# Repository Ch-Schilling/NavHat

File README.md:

# NavHat
NavHat or Navigaion Hat is a Raspberry Pi HAT made for saling boats. The HAT implements a number of features to make the Raspberry Pi suitable for a sailing boat environment. It provides power to the Raspberry Pi from board supply, collects data from NMEA bus and attached sensors. It provides the hardware base for an Open Source Navigation platform.

**Features:**
* Powered by board supply of 12-28V DC
* Onboard fuses for Raspberry and power outputs
* Four Power Outputs of up to 6A with current and temperature monitoring
* Very low sleep current
* Wake-up by key or RTC
* barometric sensor
* CAN interface for NMEA2000 network
* RS232 and RS422 interfaces for NMEA0183 devices
* Sensor interfaces with STEMMA and Qwiic compatibility
* Designed for compatibility to Raspberry Pi HAT specification

The board is designed using KiCad. 
For more details, see the corresponding [documentation](./documentation/NavHAT.md).

I hope you like the project as much as I do. In case of interest of the board itself, please contact me.

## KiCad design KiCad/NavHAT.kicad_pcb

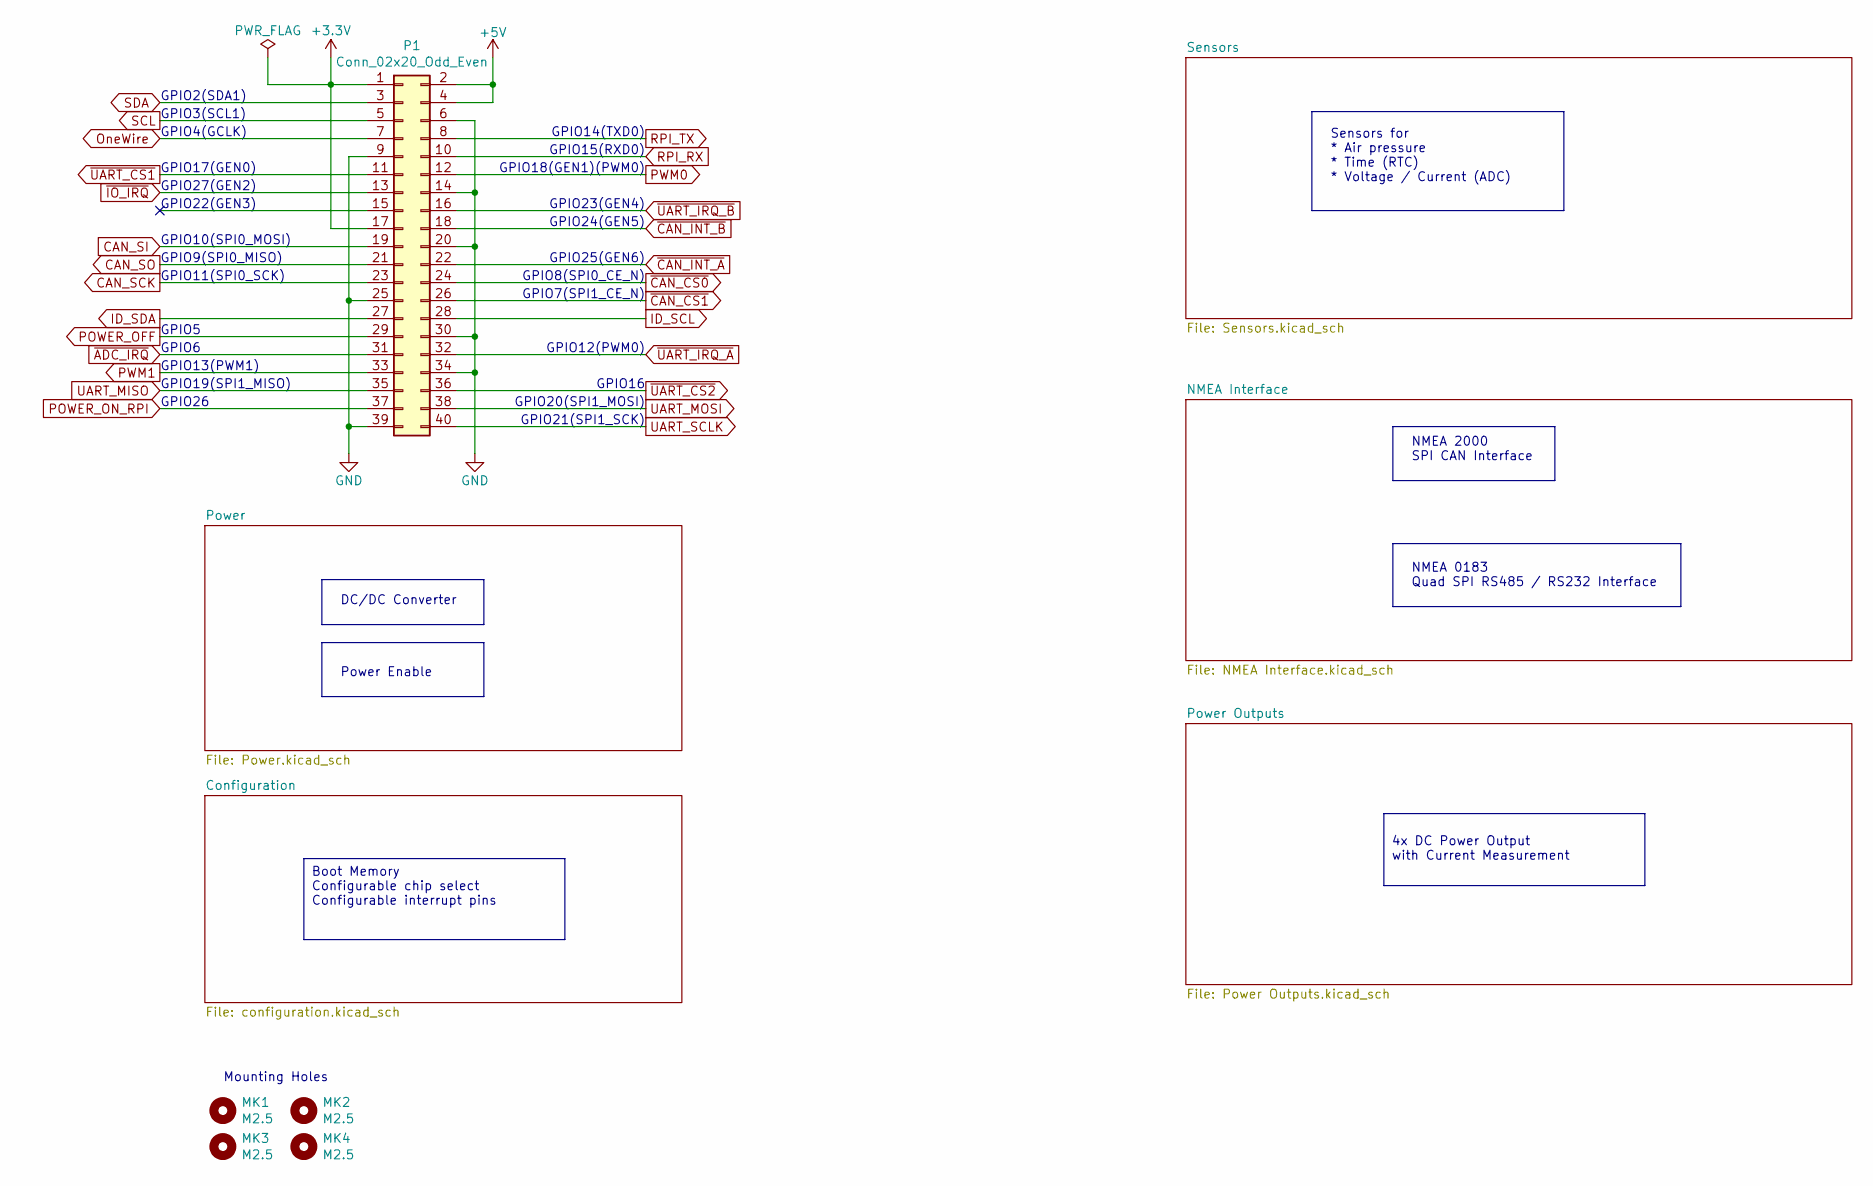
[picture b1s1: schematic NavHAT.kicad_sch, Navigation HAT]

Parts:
MK1, MK2, MK3, MK4: M2.5; MountingHole_2.7mm_M2.5
P1: Conn_02x20_Odd_Even; PinSocket_2x20_P2.54mm_Vertical

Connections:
+3.3V: P1.1, P1.17; also elsewhere on the board
+5V: P1.2, P1.4; also elsewhere on the board
CAN_SCK: P1.23; also elsewhere on the board
CAN_SI: P1.19; also elsewhere on the board
CAN_SO: P1.21; also elsewhere on the board
GND: P1.6, P1.9, P1.14, P1.20, P1.25, P1.30, P1.34, P1.39; also elsewhere on the board
ID_SCL: P1.28; also elsewhere on the board
ID_SDA: P1.27; also elsewhere on the board
OneWire: P1.7; also elsewhere on the board
POWER_OFF: P1.29; also elsewhere on the board
POWER_ON_RPI: P1.37; also elsewhere on the board
PWM0: P1.12; also elsewhere on the board
PWM1: P1.33; also elsewhere on the board
RPI_RX: P1.10; also elsewhere on the board
RPI_TX: P1.8; also elsewhere on the board
SCL: P1.5; also elsewhere on the board
SDA: P1.3; also elsewhere on the board
UART_MISO: P1.35; also elsewhere on the board
UART_MOSI: P1.38; also elsewhere on the board
UART_SCLK: P1.40; also elsewhere on the board
~ADC_IRQ: P1.31; also elsewhere on the board
~CAN_CS0: P1.24; also elsewhere on the board
~CAN_CS1: P1.26; also elsewhere on the board
~CAN_INT_A: P1.22; also elsewhere on the board
~CAN_INT_B: P1.18; also elsewhere on the board
~IO_IRQ: P1.13; also elsewhere on the board
~UART_CS1: P1.11; also elsewhere on the board
~UART_CS2: P1.36; also elsewhere on the board
~UART_IRQ_A: P1.32; also elsewhere on the board
~UART_IRQ_B: P1.16; also elsewhere on the board

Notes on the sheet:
Boot Memory Configurable chip select Configurable interrupt pins
4x DC Power Output with Current Measurement
NMEA 2000 SPI CAN Interface
GPIO26
GPIO8(SPI0_CE_N)
GPIO18(GEN1)(PWM0)
GPIO14(TXD0)
GPIO2(SDA1)
GPIO22(GEN3)
GPIO10(SPI0_MOSI)
GPIO16
GPIO6
Power Enable
GPIO5
GPIO23(GEN4)
GPIO3(SCL1)
GPIO9(SPI0_MISO)
Mounting Holes
GPIO24(GEN5)
GPIO11(SPI0_SCK)
GPIO13(PWM1)
GPIO21(SPI1_SCK)
GPIO20(SPI1_MOSI)
NMEA 0183 Quad SPI RS485 / RS232 Interface
GPIO17(GEN0)
GPIO7(SPI1_CE_N)
GPIO4(GCLK)
GPIO19(SPI1_MISO)
GPIO12(PWM0)
Sensors for * Air pressure * Time (RTC) * Voltage / Current (ADC)
GPIO25(GEN6)
GPIO27(GEN2)
GPIO15(RXD0)
DC/DC Converter

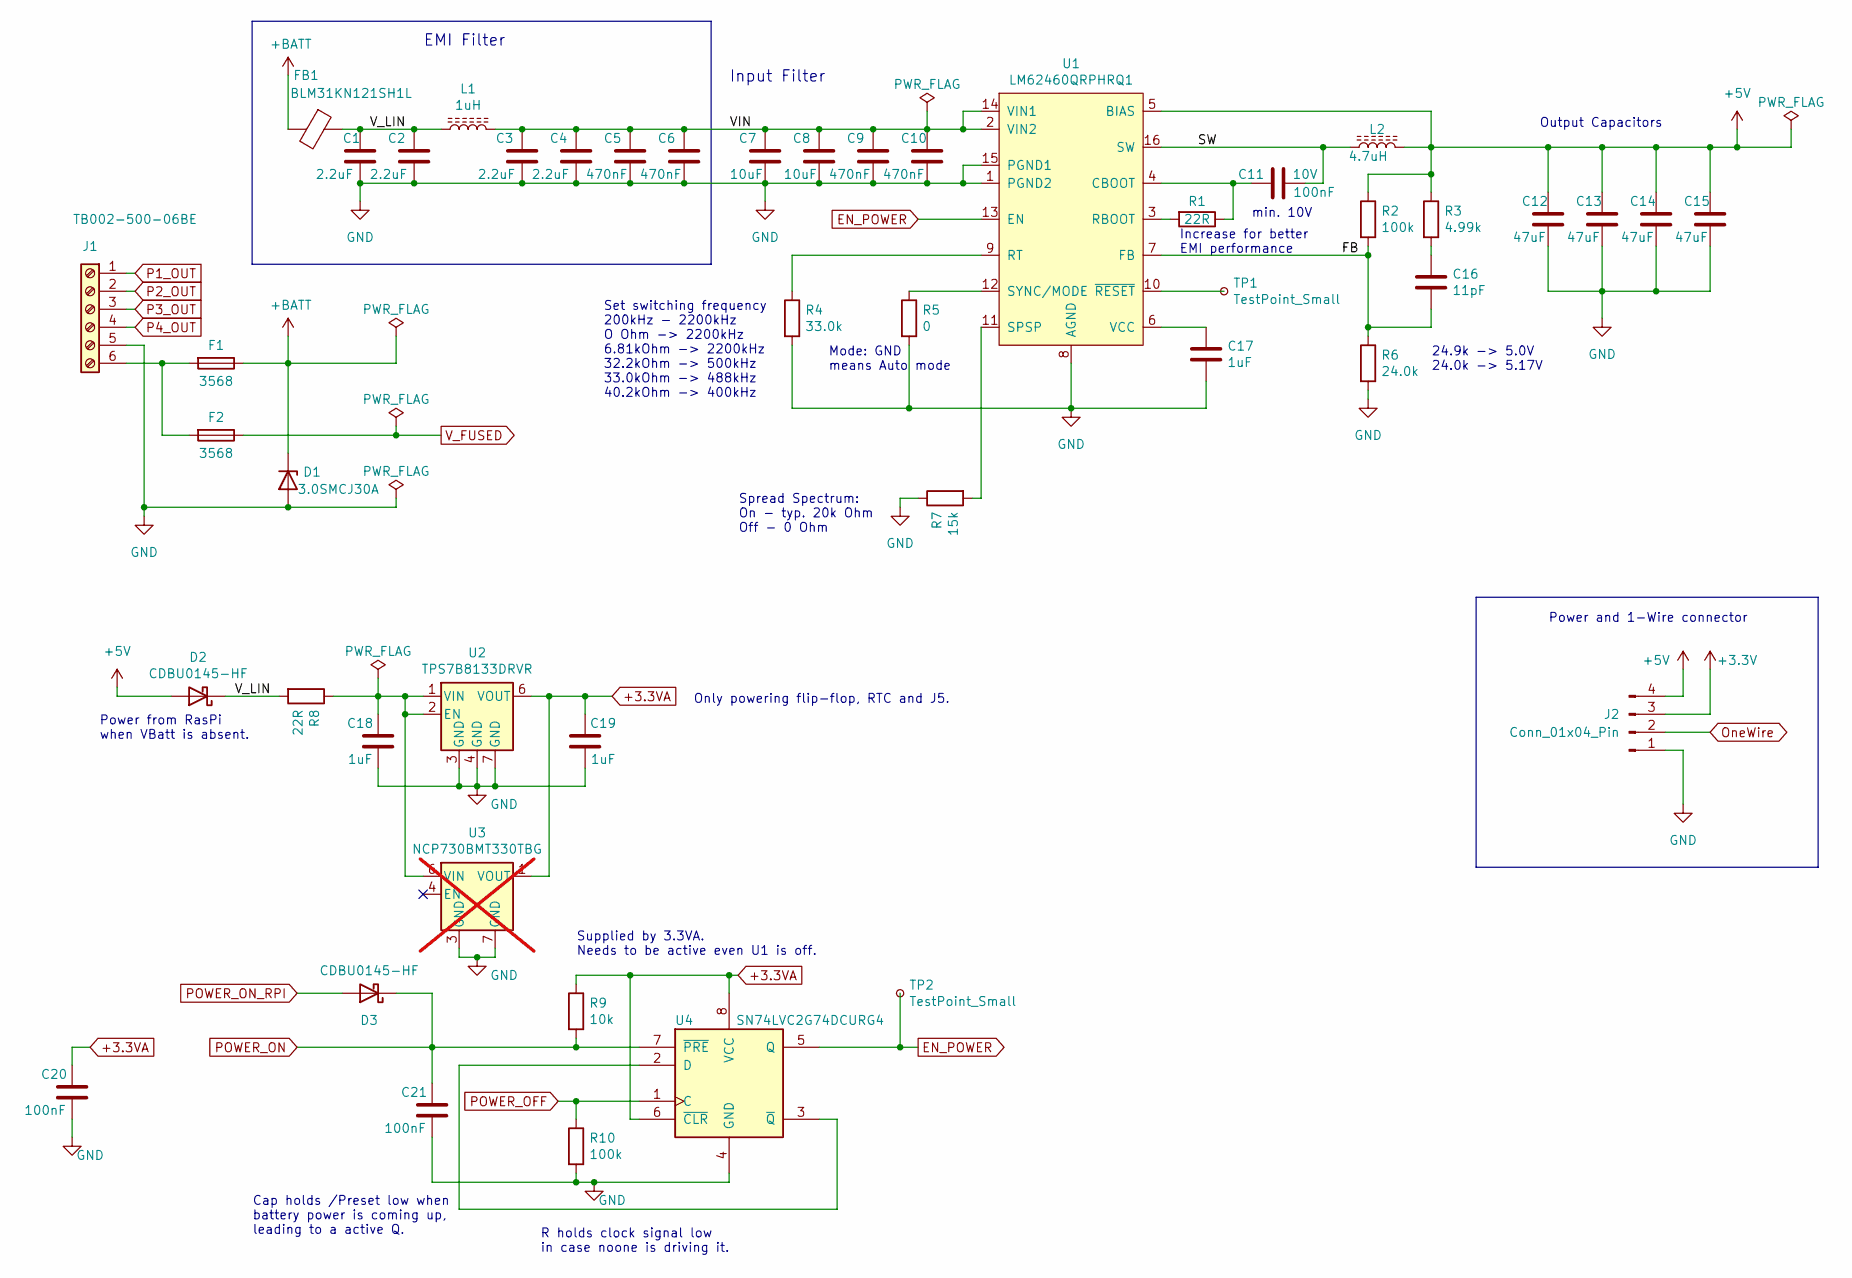
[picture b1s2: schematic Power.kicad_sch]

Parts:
C1, C2, C3, C4: 2.2uF; C_1210_3225Metric; Voltage Rating 50V
C5, C6, C9, C10: 470nF; C_0603_1608Metric; Voltage Rating 50V
C7, C8: 10uF; C_1210_3225Metric; Voltage Rating 50V
C11: 100nF; C_0402_1005Metric; Voltage Rating 10V
C12, C13, C14, C15: 47uF; C_1210_3225Metric; Voltage Rating 10V
C16: 11pF; C_0402_1005Metric
C17: 1uF; C_0603_1608Metric
C18: 1uF; C_0402_1005Metric; Voltage Rating 50V
C19: 1uF; C_0402_1005Metric
C20, C21: 100nF; C_0402_1005Metric
D1: 3.0SMCJ30A; D_SMC; Voltage Rating 30V
D2, D3: CDBU0145-HF; D_0603_1608Metric
F1, F2: 3568; Fuseholder_Blade_Mini_Keystone_3568
FB1: BLM31KN121SH1L; C_1206_3216Metric
J1: TB002-500-06BE; TerminalBlock_Phoenix_MKDS-1,5-6_1x06_P5.00mm_Horizontal
J2: Conn_01x04_Pin; PinHeader_1x04_P2.54mm_Vertical
L1: 1uH; WE-LHMI-5030; MPN 74437336010
L2: 4.7uH; WE-XHMI-6060; MPN 74439346047
R1, R8: 22R; R_0402_1005Metric
R2, R10: 100k; R_0402_1005Metric
R3: 4.99k; R_0402_1005Metric
R4: 33.0k; R_0402_1005Metric
R5: 0; R_0402_1005Metric
R6: 24.0k; R_0402_1005Metric
R7: 15k; R_0402_1005Metric
R9: 10k; R_0402_1005Metric
TP1, TP2: TestPoint_Small; TestPoint_THTPad_D1.0mm_Drill0.5mm
U1: LM62460QRPHRQ1; VQFN-HR-16
U2: TPS7B8133DRVR; DFN-6-1EP_2x2mm_P0.65mm_EP1x1.6mm
U3: NCP730BMT330TBG; DFN-6-1EP_2x2mm_P0.65mm_EP1x1.6mm; not fitted
U4: SN74LVC2G74DCURG4; VSSOP-8_2.4x2.1mm_P0.5mm

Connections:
+3.3V: J2.3; also elsewhere on the board
+3.3VA: C19.2, C20.2, R9.1, U2.6 (VOUT), U3.1 (VOUT), U4.6 (~CLR), U4.8 (VCC); also elsewhere on the board
+5V: C12.1, C13.1, C14.1, C15.1, D2.2 (A), J2.4, L2.2, R2.1, R3.1, U1.5 (BIAS); also elsewhere on the board
+BATT: D1.1 (K), F1.1, FB1.2
/Power/FB: C16.2, R2.2, R6.1, U1.7 (FB)
/Power/SW: C11.1, L2.1, U1.16 (SW)
/Power/VIN: C3.1, C4.1, C5.1, C6.1, C7.1, C8.1, C9.1, C10.1, L1.2, U1.2 (VIN2), U1.14 (VIN1)
/Power/V_LIN: C1.1, C2.1, D2.1 (K), FB1.1, L1.1, R8.2
EN_POWER: TP2.1, U1.13 (EN), U4.5 (Q)
GND: C1.2, C2.2, C3.2, C4.2, C5.2, C6.2, C7.2, C8.2, C9.2, C10.2, C12.2, C13.2, C14.2, C15.2, C17.2, C18.1, C19.1, C20.1, C21.1, D1.2 (A), J1.5, J2.1, R4.2, R5.2, R6.2, R7.1, R10.2, U1.1 (PGND2), U1.8 (AGND), U1.15 (PGND1), U2.3 (GND), U2.4 (GND), U2.7 (GND), U3.3 (GND), U3.7 (GND), U4.4 (GND); also elsewhere on the board
unnamed: C16.1, R3.2
unnamed: F1.2, F2.2, J1.6
unnamed: C11.2, R1.1, U1.4 (CBOOT)
unnamed: R1.2, U1.3 (RBOOT)
unnamed: R4.1, U1.9 (RT)
unnamed: R7.2, U1.11 (SPSP)
unnamed: R5.1, U1.12 (SYNC/MODE)
unnamed: C17.1, U1.6 (VCC)
unnamed: TP1.1, U1.10 (~RESET)
unnamed: C18.2, R8.1, U2.1 (VIN), U2.2 (EN), U3.6 (VIN)
unnamed: U4.2 (D), U4.3 (~Q)
OneWire: J2.2; also elsewhere on the board
P1_OUT: J1.1; also elsewhere on the board
P2_OUT: J1.2; also elsewhere on the board
P3_OUT: J1.3; also elsewhere on the board
P4_OUT: J1.4; also elsewhere on the board
POWER_OFF: R10.1, U4.1 (C); also elsewhere on the board
POWER_ON: C21.2, D3.1 (K), R9.2, U4.7 (~PRE); also elsewhere on the board
POWER_ON_RPI: D3.2 (A); also elsewhere on the board
V_FUSED: F2.1; also elsewhere on the board

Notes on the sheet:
Increase for better EMI performance
Only powering flip-flop, RTC and J5.
Spread Spectrum: On - typ. 20k Ohm Off - 0 Ohm
Supplied by 3.3VA. Needs to be active even U1 is off.
Output Capacitors
Power and 1-Wire connector
Input Filter
min. 10V
EMI Filter
Power from RasPi when VBatt is absent.
Mode: GND means Auto mode
Set switching frequency 200kHz - 2200kHz O Ohm -> 2200kHz 6.81kOhm -> 2200kHz 32.2kOhm -> 500kHz 33.0kOhm -> 488kHz 40.2kOhm -> 400kHz
Cap holds /Preset low when battery power is coming up, leading to a active Q.
R holds clock signal low in case noone is driving it.
24.9k -> 5.0V 24.0k -> 5.17V

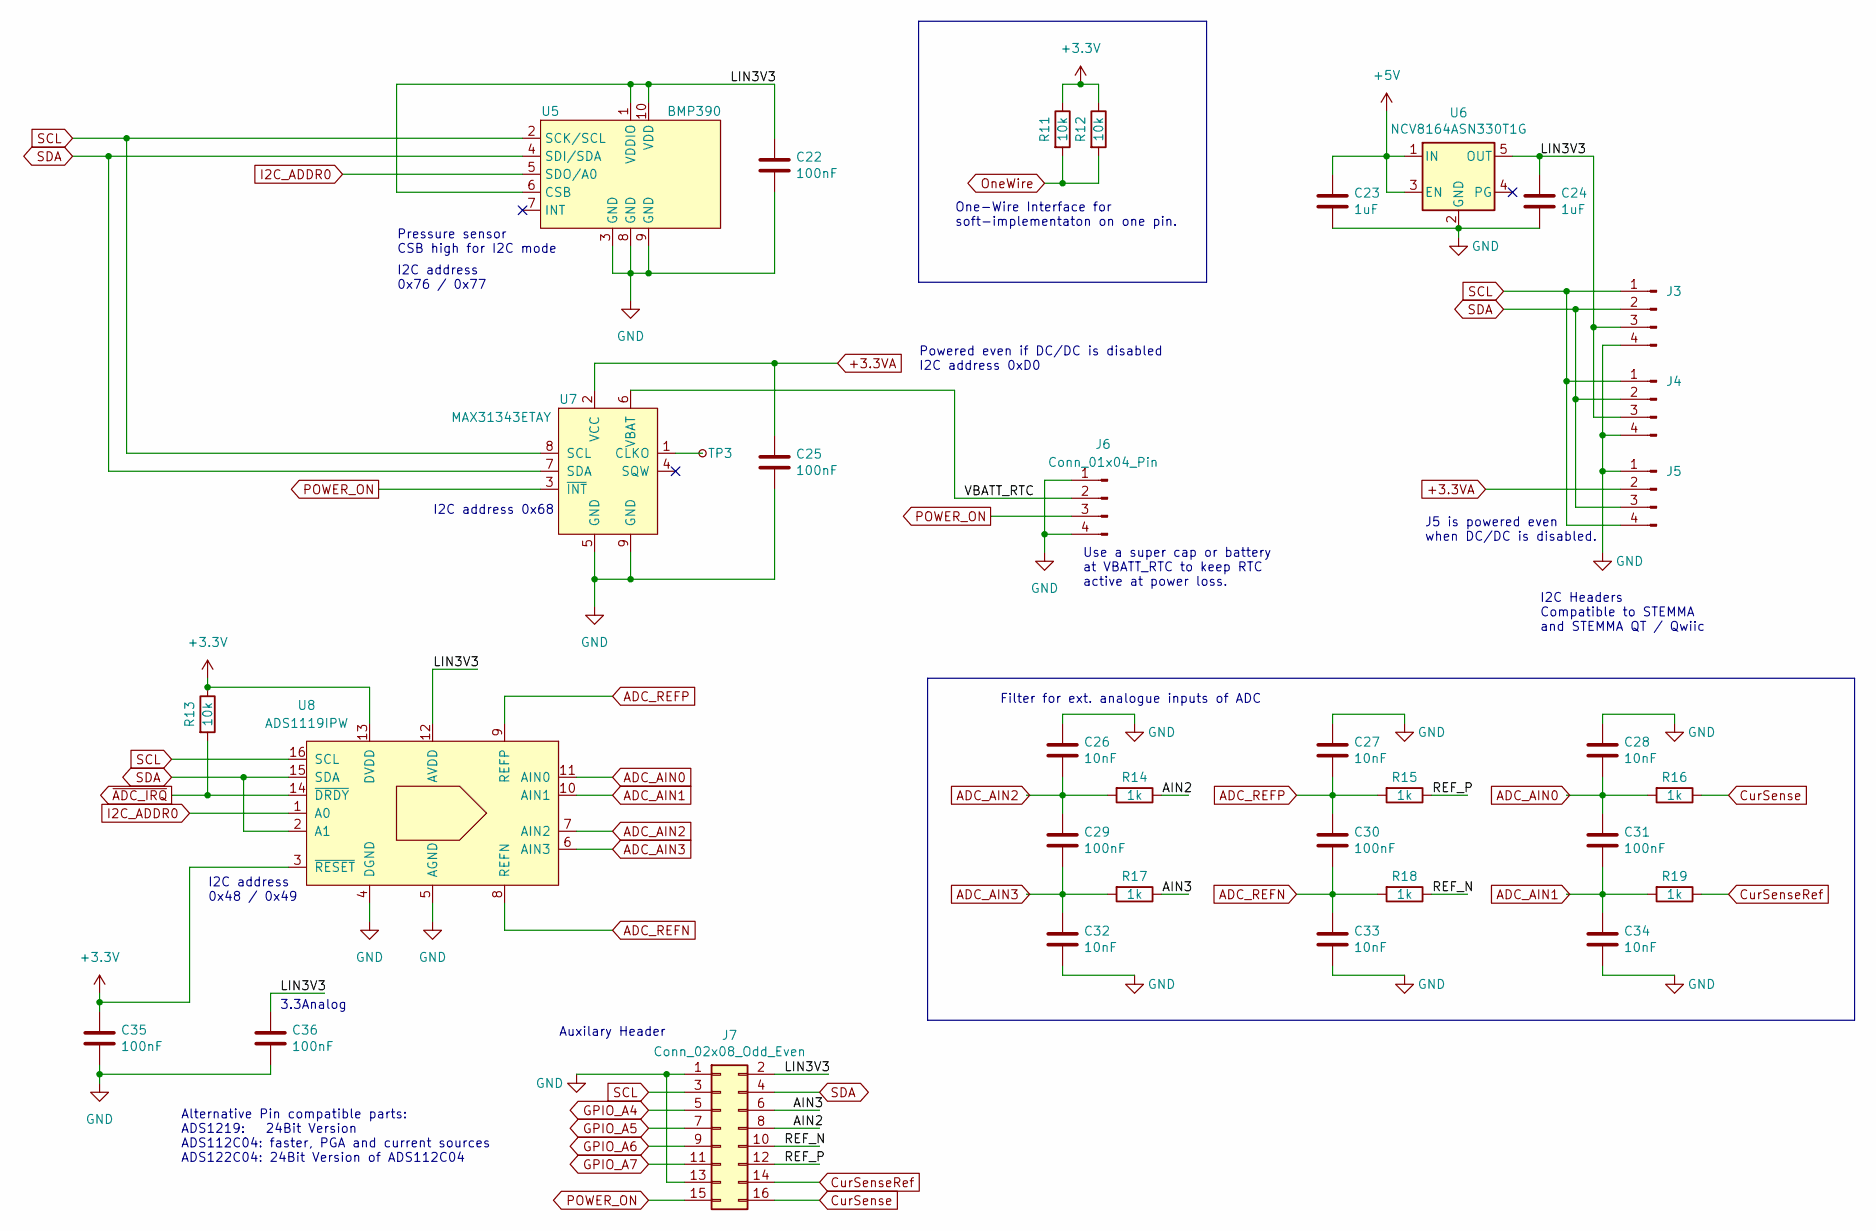
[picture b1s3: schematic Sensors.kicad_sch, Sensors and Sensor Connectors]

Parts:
C22, C25, C29, C30, C31, C35, C36: 100nF; C_0402_1005Metric
C23, C24: 1uF; C_0402_1005Metric
C26, C27, C28, C32, C33, C34: 10nF; C_0402_1005Metric
J3, J4: B4B-PH-K-S; JST_PH_B4B-PH-K_1x04_P2.00mm_Vertical
J5: SM04B-SRSS-TB; JST_SH_SM04B-SRSS-TB_1x04-1MP_P1.00mm_Horizontal
J6: Conn_01x04_Pin; PinHeader_1x04_P2.54mm_Vertical
J7: Conn_02x08_Odd_Even; PinHeader_2x08_P1.27mm_Vertical
R11, R12, R13: 10k; R_0402_1005Metric
R14, R15, R16, R17, R18, R19: 1k; R_0402_1005Metric
TP3: TestPoint_Small; TestPoint_THTPad_D1.0mm_Drill0.5mm
U5: BMP390; Bosch_LGA-10_2x2mm_P0.5mm
U6: NCV8164ASN330T1G; TSOP-5_1.65x3.05mm_P0.95mm
U7: MAX31343ETAY; SW-TDFN-8-1EP_3x4mm_P0.65mm_EP2.7x2.3mm
U8: ADS1119IPW; TSSOP-16_4.4x5mm_P0.65mm

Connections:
+3.3V: C35.1, R11.1, R12.1, R13.1, U8.3 (~RESET), U8.13 (DVDD); also elsewhere on the board
+3.3VA: C25.1, J5.2, U7.2 (VCC); also elsewhere on the board
+5V: C23.1, U6.1 (IN), U6.3 (EN); also elsewhere on the board
/Sensors/AIN2: J7.8, R14.1
/Sensors/AIN3: J7.6, R17.1
/Sensors/LIN3V3: C22.1, C24.1, C36.1, J3.3, J4.3, J7.2, U5.1 (VDDIO), U5.6 (CSB), U5.10 (VDD), U6.5 (OUT), U8.12 (AVDD)
/Sensors/REF_N: J7.10, R18.1
/Sensors/REF_P: J7.12, R15.1
/Sensors/VBATT_RTC: J6.2, U7.6 (VBAT)
ADC_AIN0: C28.2, C31.1, R16.2, U8.11 (AIN0)
ADC_AIN1: C31.2, C34.1, R19.2, U8.10 (AIN1)
ADC_AIN2: C26.2, C29.1, R14.2, U8.7 (AIN2)
ADC_AIN3: C29.2, C32.1, R17.2, U8.6 (AIN3)
ADC_REFN: C30.2, C33.1, R18.2, U8.8 (REFN)
ADC_REFP: C27.2, C30.1, R15.2, U8.9 (REFP)
CurSense: J7.16, R16.1; also elsewhere on the board
CurSenseRef: J7.14, R19.1; also elsewhere on the board
GND: C22.2, C23.2, C24.2, C25.2, C26.1, C27.1, C28.1, C32.2, C33.2, C34.2, C35.2, C36.2, J3.4, J4.4, J5.1, J6.1, J6.4, J7.1, J7.13, U5.3 (GND), U5.8 (GND), U5.9 (GND), U6.2 (GND), U7.5 (GND), U7.9 (GND), U8.4 (DGND), U8.5 (AGND); also elsewhere on the board
GPIO_A4: J7.5; also elsewhere on the board
GPIO_A5: J7.7; also elsewhere on the board
GPIO_A6: J7.9; also elsewhere on the board
GPIO_A7: J7.11; also elsewhere on the board
I2C_ADDR0: U5.5 (SDO/A0), U8.1 (A0); also elsewhere on the board
unnamed: TP3.1, U7.1 (CLKO)
OneWire: R11.2, R12.2; also elsewhere on the board
POWER_ON: J6.3, J7.15, U7.3 (~INT); also elsewhere on the board
SCL: J3.1, J4.1, J5.4, J7.3, U5.2 (SCK/SCL), U7.8 (SCL), U8.16 (SCL); also elsewhere on the board
SDA: J3.2, J4.2, J5.3, J7.4, U5.4 (SDI/SDA), U7.7 (SDA), U8.2 (A1), U8.15 (SDA); also elsewhere on the board
~ADC_IRQ: R13.2, U8.14 (~DRDY); also elsewhere on the board

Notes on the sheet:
I2C address 0x76 / 0x77
J5 is powered even when DC/DC is disabled.
I2C address 0x48 / 0x49
3.3Analog
I2C Headers Compatible to STEMMA and STEMMA QT / Qwiic
Pressure sensor CSB high for I2C mode
Use a super cap or battery at VBATT_RTC to keep RTC active at power loss.
One-Wire Interface for soft-implementaton on one pin.
Auxilary Header
Filter for ext. analogue inputs of ADC
I2C address 0x68
Powered even if DC/DC is disabled I2C address 0xD0
Alternative Pin compatible parts: ADS1219: 24Bit Version ADS112C04: faster, PGA and current sources ADS122C04: 24Bit Version of ADS112C04

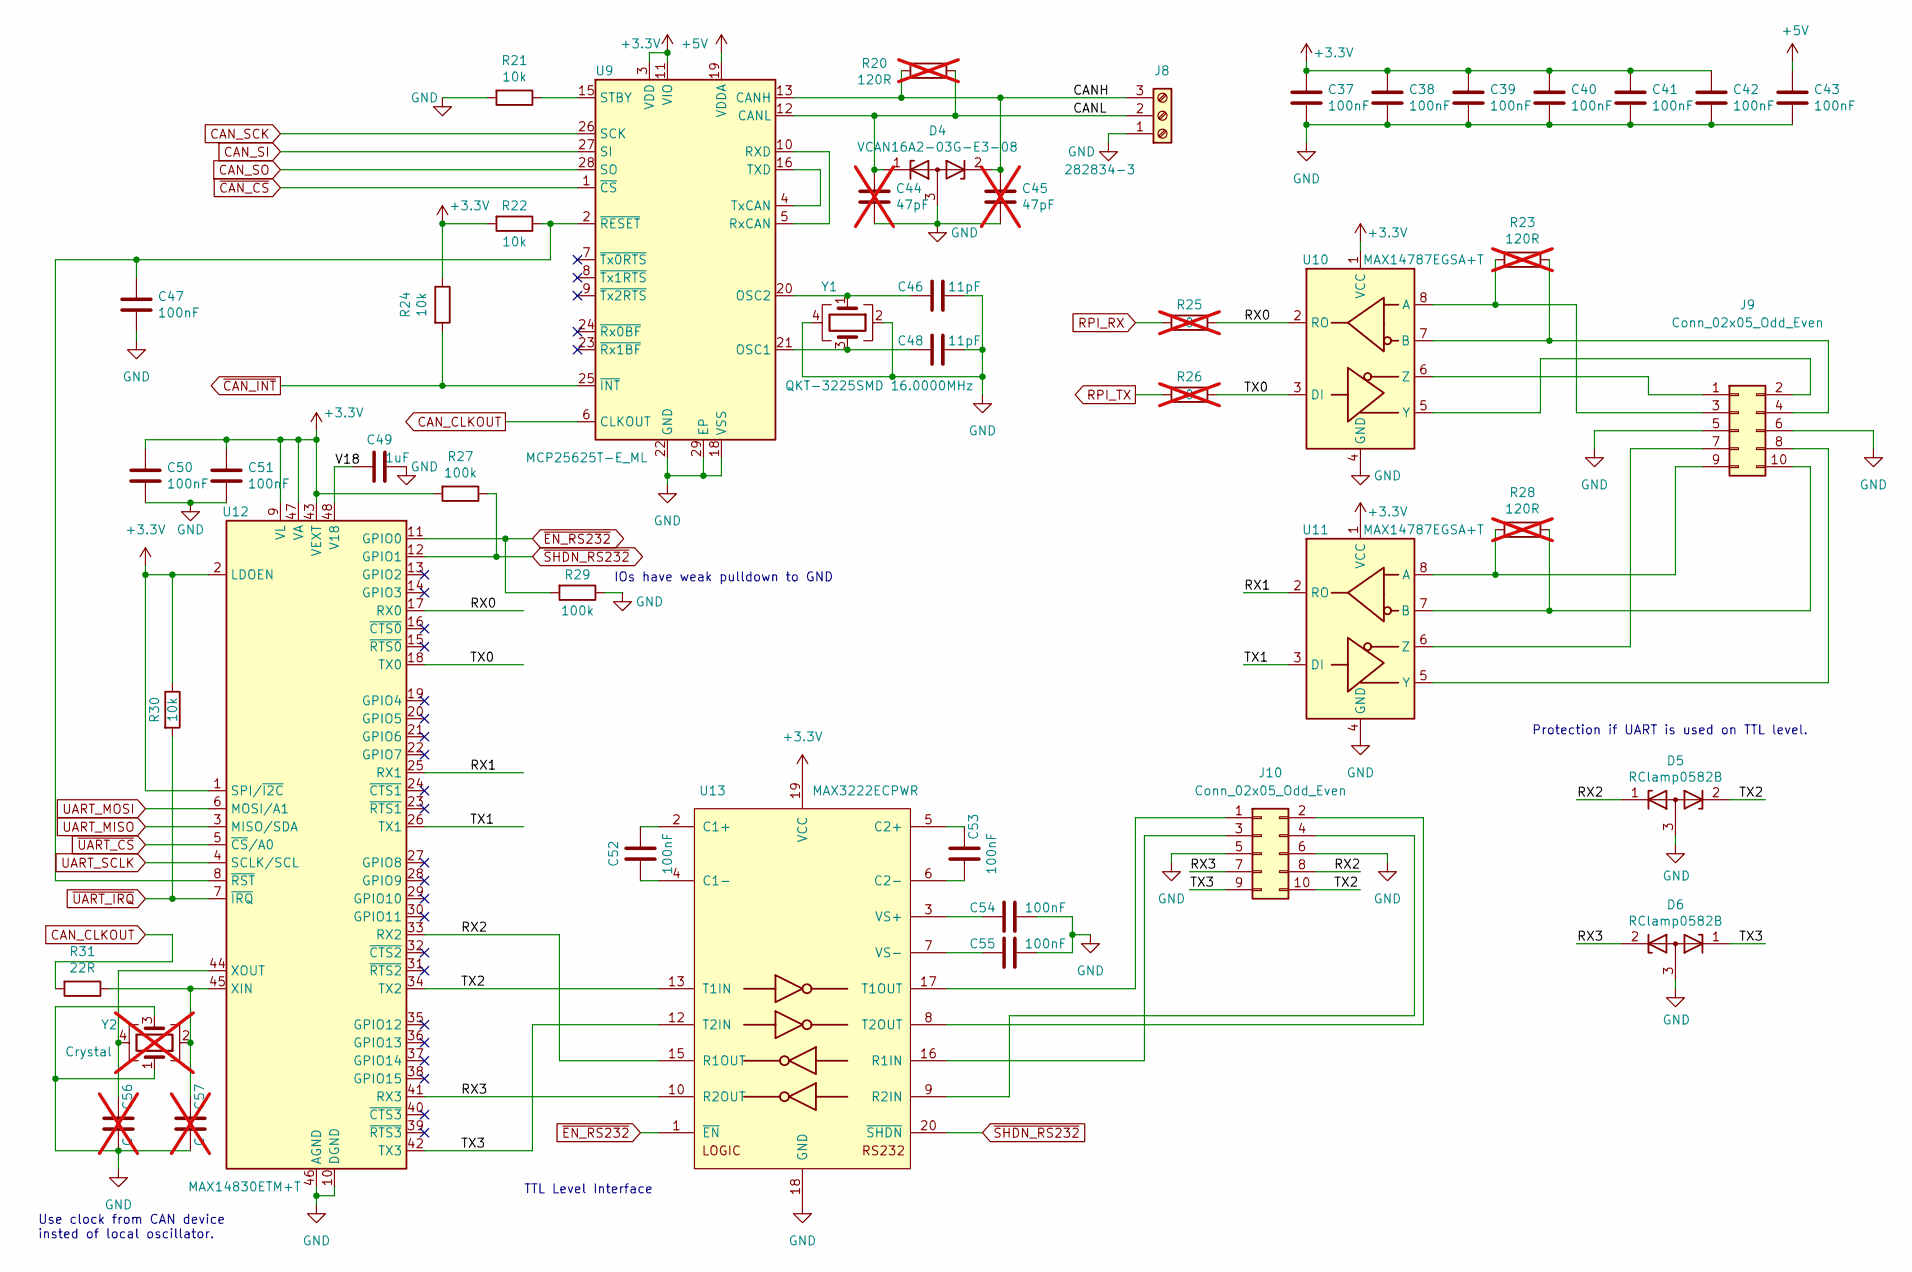
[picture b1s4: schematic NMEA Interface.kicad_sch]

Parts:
C37, C38, C39, C40, C41, C42, C43, C47, C50, C51, C52, C53, C54, C55: 100nF; C_0402_1005Metric
C44, C45: 47pF; C_0402_1005Metric; not fitted
C46, C48: 11pF; C_0402_1005Metric
C49: 1uF; C_0402_1005Metric
C56, C57: C; C_0402_1005Metric; not fitted
D4: VCAN16A2-03G-E3-08; SOT-323_SC-70
D5, D6: RClamp0582B; SOT-523
J8: 282834-3; TerminalBlock_TE_282834-3_1x03_P2.54mm_Horizontal
J9: Conn_02x05_Odd_Even; PinHeader_2x05_P2.54mm_Vertical
J10: Conn_02x05_Odd_Even; PinHeader_2x05_P1.27mm_Vertical
R20: 120R; R_0603_1608Metric; not fitted
R21, R22, R24, R30: 10k; R_0402_1005Metric
R23, R28: 120R; R_1206_3216Metric; not fitted
R25, R26: 0; R_0402_1005Metric; not fitted
R27, R29: 100k; R_0402_1005Metric
R31: 22R; R_0402_1005Metric
U9: MCP25625T-E_ML; QFN-28-1EP_6x6mm_P0.65mm_EP4.25x4.25mm_ThermalVias
U10, U11: MAX14787EGSA+T; SOIC-8_3.9x4.9mm_P1.27mm
U12: MAX14830ETM+T; TQFN-48-1EP_7x7mm_P0.5mm_EP5.1x5.1mm
U13: MAX3222ECPWR; TSSOP-20_4.4x6.5mm_P0.65mm
Y1: QKT-3225SMD 16.0000MHz; Crystal_SMD_3225-4Pin_3.2x2.5mm
Y2: Crystal; Crystal_SMD_3225-4Pin_3.2x2.5mm; not fitted

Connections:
+3.3V: C37.1, C38.1, C39.1, C40.1, C41.1, C42.1, C50.1, C51.1, R22.2, R24.1, R27.2, R30.1, U9.3 (VDD), U9.11 (VIO), U10.1 (VCC), U11.1 (VCC), U12.1 (SPI/~I2C), U12.2 (LDOEN), U12.9 (VL), U12.43 (VEXT), U12.47 (VA), U13.19 (VCC); also elsewhere on the board
+5V: C43.1, U9.19 (VDDA); also elsewhere on the board
/NMEA Interface/CANH: C45.1, D4.2 (K), J8.3, R20.2, U9.13 (CANH)
/NMEA Interface/CANL: C44.1, D4.1 (K), J8.2, R20.1, U9.12 (CANL)
/NMEA Interface/RX0: R25.1, U10.2 (RO), U12.17 (RX0)
/NMEA Interface/RX1: U11.2 (RO), U12.25 (RX1)
/NMEA Interface/RX2: D5.1 (K), J10.8, U12.33 (RX2), U13.15 (R1OUT)
/NMEA Interface/RX3: D6.2 (K), J10.7, U12.41 (RX3), U13.10 (R2OUT)
/NMEA Interface/TX0: R26.1, U10.3 (DI), U12.18 (TX0)
/NMEA Interface/TX1: U11.3 (DI), U12.26 (TX1)
/NMEA Interface/TX2: D5.2 (K), J10.10, U12.34 (TX2), U13.13 (T1IN)
/NMEA Interface/TX3: D6.1 (K), J10.9, U12.42 (TX3), U13.12 (T2IN)
/NMEA Interface/V18: C49.2, U12.48 (V18)
CAN_CLKOUT: R31.2, U9.6 (CLKOUT)
CAN_SCK: U9.26 (SCK); also elsewhere on the board
CAN_SI: U9.27 (SI); also elsewhere on the board
CAN_SO: U9.28 (SO); also elsewhere on the board
GND: C37.2, C38.2, C39.2, C40.2, C41.2, C42.2, C43.2, C44.2, C45.2, C46.1, C47.2, C48.1, C49.1, C50.2, C51.2, C54.1, C55.1, C56.1, C57.1, D4.3 (A), D5.3 (A), D6.3 (A), J8.1, J9.5, J9.6, J10.5, J10.6, R21.2, R29.1, U9.18 (VSS), U9.22 (GND), U9.29 (EP), U10.4 (GND), U11.4 (GND), U12.10 (DGND), U12.46 (AGND), U12.49 (AGND), U13.18 (GND), Y1.2, Y1.4, Y2.1, Y2.3; also elsewhere on the board
unnamed: J9.1, U10.6 (Z)
unnamed: J9.2, U10.5 (Y)
unnamed: J9.3, R23.2, U10.8 (A)
unnamed: J9.4, R23.1, U10.7 (B)
unnamed: J9.7, U11.6 (Z)
unnamed: J9.8, U11.5 (Y)
unnamed: J9.9, R28.2, U11.8 (A)
unnamed: J9.10, R28.1, U11.7 (B)
unnamed: J10.1, U13.17 (T1OUT)
unnamed: J10.2, U13.8 (T2OUT)
unnamed: J10.3, U13.16 (R1IN)
unnamed: J10.4, U13.9 (R2IN)
unnamed: C48.2, U9.21 (OSC1), Y1.3
unnamed: C46.2, U9.20 (OSC2), Y1.1
unnamed: U9.5 (RxCAN), U9.10 (RXD)
unnamed: R21.1, U9.15 (STBY)
unnamed: U9.4 (TxCAN), U9.16 (TXD)
unnamed: C57.2, R31.1, U12.45 (XIN), Y2.2
unnamed: C56.2, U12.44 (XOUT), Y2.4
unnamed: C47.1, R22.1, U9.2 (~RESET), U12.8 (~RST)
unnamed: C52.2, U13.2 (C1+)
unnamed: C52.1, U13.4 (C1-)
unnamed: C53.2, U13.5 (C2+)
unnamed: C53.1, U13.6 (C2-)
unnamed: C54.2, U13.3 (VS+)
unnamed: C55.2, U13.7 (VS-)
RPI_RX: R25.2; also elsewhere on the board
RPI_TX: R26.2; also elsewhere on the board
UART_MISO: U12.3 (MISO/SDA); also elsewhere on the board
UART_MOSI: U12.6 (MOSI/A1); also elsewhere on the board
UART_SCLK: U12.4 (SCLK/SCL); also elsewhere on the board
~CAN_CS: U9.1 (~CS); also elsewhere on the board
~CAN_INT: R24.2, U9.25 (~INT); also elsewhere on the board
~EN_RS232: R29.2, U12.11 (GPIO0), U13.1 (~EN)
~SHDN_RS232: R27.1, U12.12 (GPIO1), U13.20 (~SHDN)
~UART_CS: U12.5 (~CS/A0); also elsewhere on the board
~UART_IRQ: R30.2, U12.7 (~IRQ); also elsewhere on the board

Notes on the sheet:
TTL Level Interface
Use clock from CAN device insted of local oscillator.
Protection if UART is used on TTL level.
IOs have weak pulldown to GND

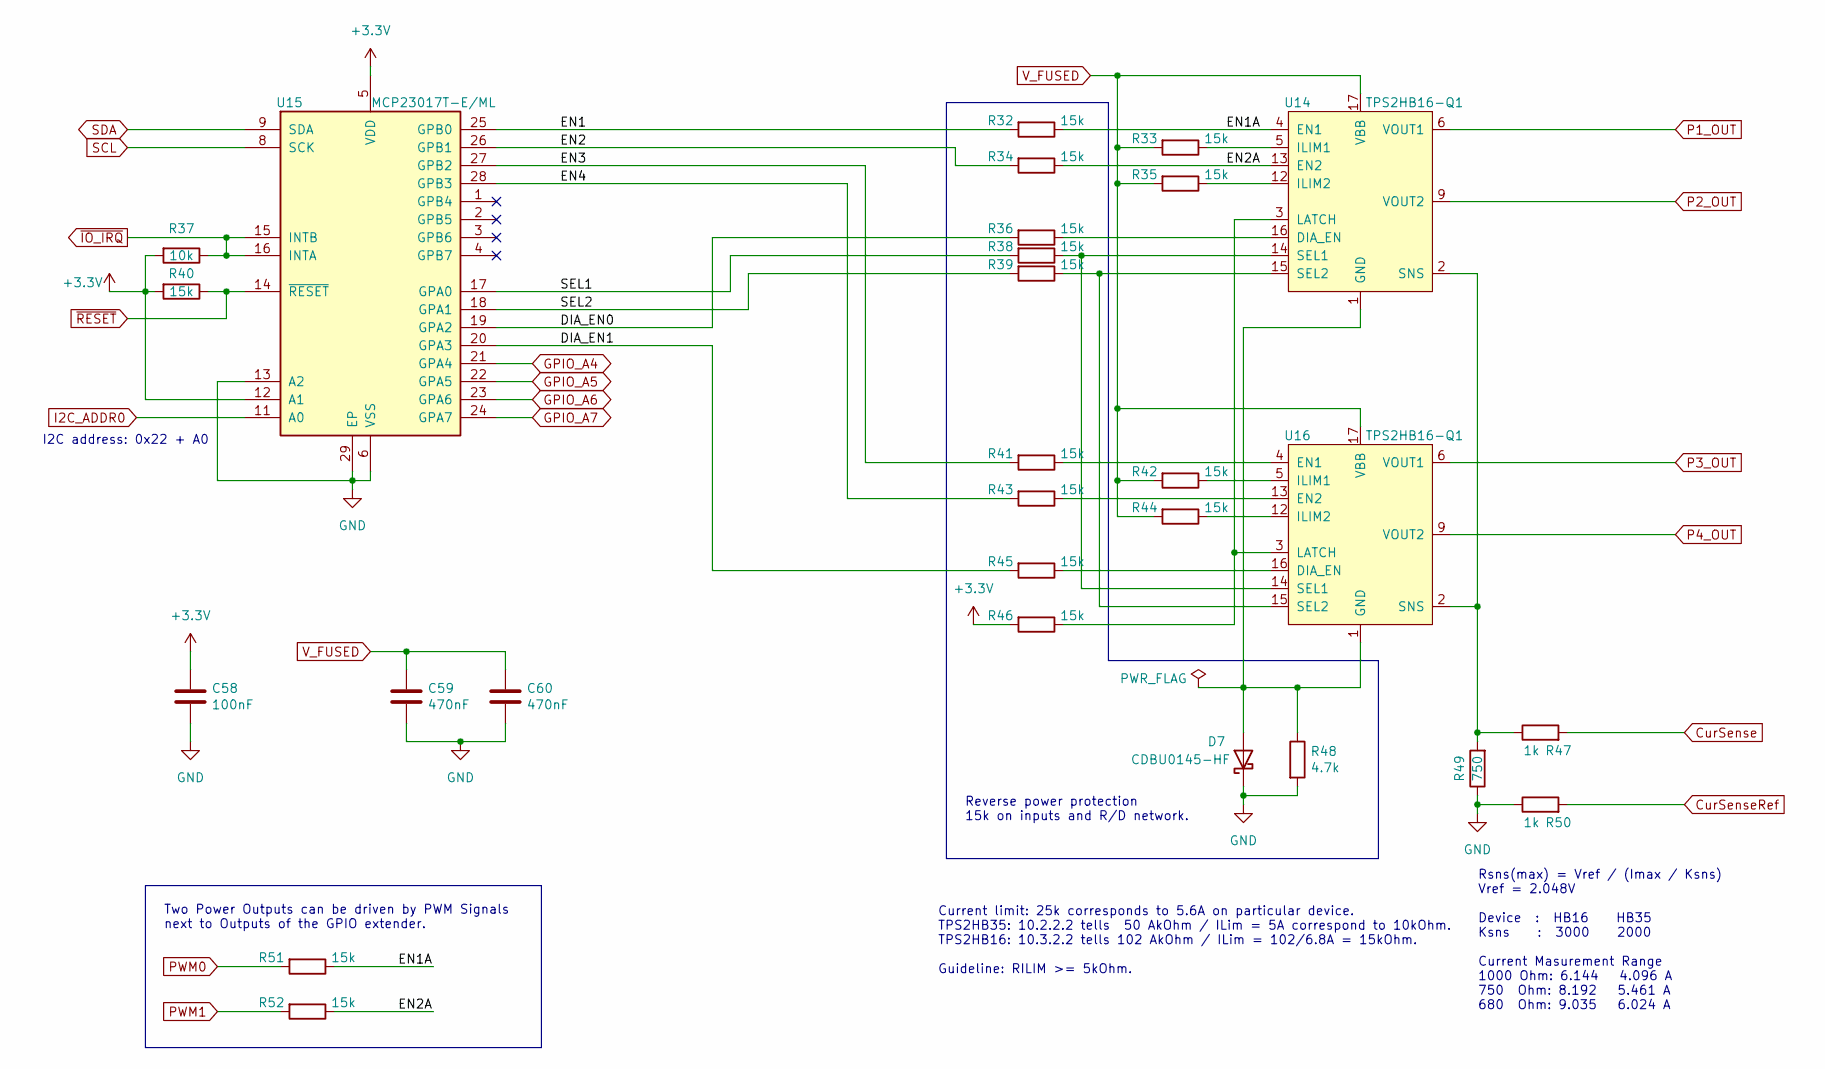
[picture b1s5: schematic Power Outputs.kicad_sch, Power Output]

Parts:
C58: 100nF; C_0402_1005Metric
C59, C60: 470nF; C_0603_1608Metric; Voltage Rating 50V
D7: CDBU0145-HF; D_0603_1608Metric
R32, R33, R34, R35, R36, R38, R39, R40, R41, R42, R43, R44, R45, R46, R51, R52: 15k; R_0402_1005Metric
R37: 10k; R_0402_1005Metric
R47, R50: 1k; R_0402_1005Metric
R48: 4.7k; R_0402_1005Metric
R49: 750; R_0603_1608Metric
U14, U16: TPS2HB16-Q1; TSSOP-16-1EP_4.4x5mm_P0.65mm
U15: MCP23017T-E/ML; QFN-28-1EP_6x6mm_P0.65mm_EP4.25x4.25mm

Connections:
+3.3V: C58.1, R37.2, R40.2, R46.2, U15.5 (VDD), U15.12 (A1); also elsewhere on the board
/Power Outputs/DIA_EN0: R36.2, U15.19 (GPA2)
/Power Outputs/DIA_EN1: R45.2, U15.20 (GPA3)
/Power Outputs/EN1: R32.2, U15.25 (GPB0)
/Power Outputs/EN1A: R32.1, R51.1, U14.4 (EN1)
/Power Outputs/EN2: R34.2, U15.26 (GPB1)
/Power Outputs/EN2A: R34.1, R52.1, U14.13 (EN2)
/Power Outputs/EN3: R41.2, U15.27 (GPB2)
/Power Outputs/EN4: R43.2, U15.28 (GPB3)
/Power Outputs/SEL1: R38.2, U15.17 (GPA0)
/Power Outputs/SEL2: R39.2, U15.18 (GPA1)
CurSense: R47.2; also elsewhere on the board
CurSenseRef: R50.2; also elsewhere on the board
GND: C58.2, C59.2, C60.2, D7.1 (K), R48.2, R49.1, R50.1, U15.6 (VSS), U15.13 (A2), U15.29 (EP); also elsewhere on the board
GPIO_A4: U15.21 (GPA4); also elsewhere on the board
GPIO_A5: U15.22 (GPA5); also elsewhere on the board
GPIO_A6: U15.23 (GPA6); also elsewhere on the board
GPIO_A7: U15.24 (GPA7); also elsewhere on the board
I2C_ADDR0: U15.11 (A0); also elsewhere on the board
unnamed: D7.2 (A), R48.1, U14.1 (GND), U16.1 (GND)
unnamed: R36.1, U14.16 (DIA_EN)
unnamed: R33.1, U14.5 (ILIM1)
unnamed: R35.1, U14.12 (ILIM2)
unnamed: R46.1, U14.3 (LATCH), U16.3 (LATCH)
unnamed: R38.1, U14.14 (SEL1), U16.14 (SEL1)
unnamed: R39.1, U14.15 (SEL2), U16.15 (SEL2)
unnamed: R47.1, R49.2, U14.2 (SNS), U16.2 (SNS)
unnamed: R45.1, U16.16 (DIA_EN)
unnamed: R41.1, U16.4 (EN1)
unnamed: R43.1, U16.13 (EN2)
unnamed: R42.1, U16.5 (ILIM1)
unnamed: R44.1, U16.12 (ILIM2)
P1_OUT: U14.6 (VOUT1), U14.7 (VOUT1), U14.8 (VOUT1); also elsewhere on the board
P2_OUT: U14.9 (VOUT2), U14.10 (VOUT2), U14.11 (VOUT2); also elsewhere on the board
P3_OUT: U16.6 (VOUT1), U16.7 (VOUT1), U16.8 (VOUT1); also elsewhere on the board
P4_OUT: U16.9 (VOUT2), U16.10 (VOUT2), U16.11 (VOUT2); also elsewhere on the board
PWM0: R51.2; also elsewhere on the board
PWM1: R52.2; also elsewhere on the board
SCL: U15.8 (SCK); also elsewhere on the board
SDA: U15.9 (SDA); also elsewhere on the board
V_FUSED: C59.1, C60.1, R33.2, R35.2, R42.2, R44.2, U14.17 (VBB), U16.17 (VBB); also elsewhere on the board
~IO_IRQ: R37.1, U15.15 (INTB), U15.16 (INTA); also elsewhere on the board
~RESET: R40.1, U15.14 (~RESET)

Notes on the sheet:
Reverse power protection 15k on inputs and R/D network.
Current limit: 25k corresponds to 5.6A on particular device. TPS2HB35: 10.2.2.2 tells 50 AkOhm / ILim = 5A correspond to 10kOhm. TPS2HB16: 10.3.2.2 tells 102 AkOhm / ILim = 102/6.8A = 15kOhm. Guideline: RILIM >= 5kOhm.
Two Power Outputs can be driven by PWM Signals next to Outputs of the GPIO extender.
Rsns(max) = Vref / (Imax / Ksns) Vref = 2.048V Device : HB16 HB35 Ksns : 3000 2000 Current Masurement Range 1000 Ohm: 6.144 4.096 A 750 Ohm: 8.192 5.461 A 680 Ohm: 9.035 6.024 A
I2C address: 0x22 + A0
